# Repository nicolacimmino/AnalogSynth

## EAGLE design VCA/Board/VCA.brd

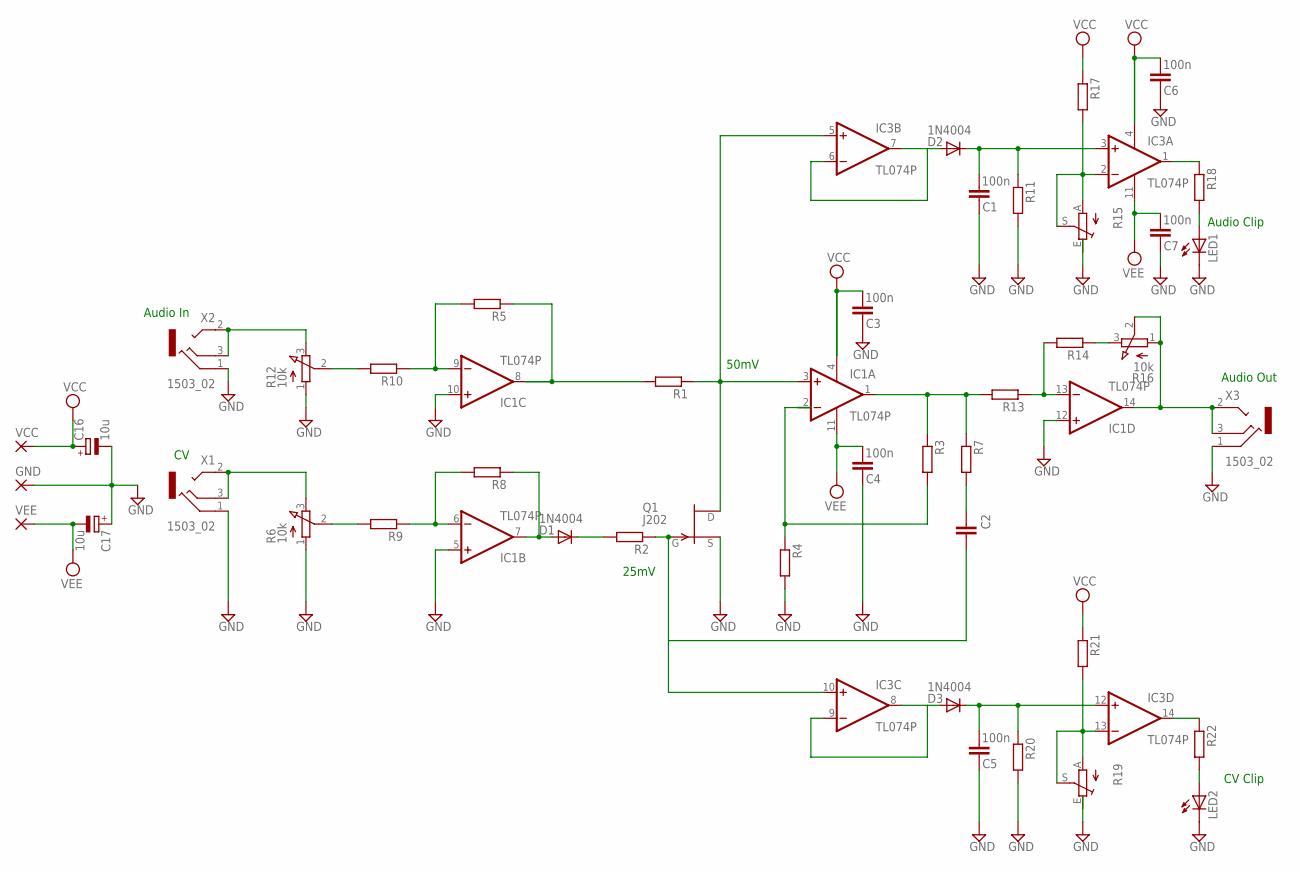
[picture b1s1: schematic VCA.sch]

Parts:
C1, C3, C4, C5, C6, C7: 100n; C5B2.5
C2: C-EU050-045X075; C050-045X075
C16, C17: 10u; E2,5-7
D1, D2, D3: 1N4004; DO41-10
GND: 3,17/1,1
IC1, IC3: TL074P; DIL14
LED1, LED2: LED5MM
Q1: J202; TO92
R1, R2, R3, R4, R5, R7, R8, R9, R10, R11, R13, R14, R17, R18, R20, R21, R22: R-EU_0207/10; 0207/10
R6, R12, R16: 10k; 3RP/1610N
R15, R19: TRIM_EU-S75P; S75P
VCC: 3,17/1,1
VEE: 3,17/1,1
X1, X2, X3: 1503_02

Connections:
GND: C1.1, C3.1, C4.1, C5.1, C6.1, C7.1, C16.-, C17.+, GND.1, IC1.5 (+IN), IC1.10 (+IN), IC1.12 (+IN), LED1.K (C), LED2.K (C), Q1.2 (S), R4.2, R6.1 (A), R11.2, R12.1 (A), R20.2, X1.1, X2.1, X3.1
unnamed: IC1.3 (+IN), IC3.5 (+IN), Q1.3 (D), R1.1
unnamed: C2.2, IC3.10 (+IN), Q1.1 (G), R2.1
unnamed: IC1.2 (-IN), R3.2, R4.1
unnamed: IC1.1 (OUT), R3.1, R7.1, R13.2
unnamed: C2.1, R7.2
unnamed: R6.2 (S), R9.2
unnamed: D1.A, IC1.7 (OUT), R8.1
unnamed: IC1.6 (-IN), R8.2, R9.1
unnamed: D1.C, R2.2
unnamed: R12.3 (E), X2.2, X2.3
unnamed: IC1.8 (OUT), R1.2, R5.1
unnamed: IC1.9 (-IN), R5.2, R10.1
unnamed: R10.2, R12.2 (S)
unnamed: IC1.13 (-IN), R13.1, R14.2
unnamed: R6.3 (E), X1.2, X1.3
unnamed: R14.1, R16.3 (E)
unnamed: IC1.14 (OUT), R16.1 (A), R16.2 (S), X3.2, X3.3
unnamed: D2.A, IC3.6 (-IN), IC3.7 (OUT)
unnamed: C1.2, D2.C, IC3.3 (+IN), R11.1
unnamed: IC3.2 (-IN), R15.A, R15.S, R17.2
unnamed: IC3.1 (OUT), R18.1
unnamed: LED1.A, R18.2
unnamed: D3.A, IC3.8 (OUT), IC3.9 (-IN)
unnamed: C5.2, D3.C, IC3.12 (+IN), R20.1
unnamed: IC3.13 (-IN), R19.A, R19.S, R21.2
unnamed: IC3.14 (OUT), R22.1
unnamed: LED2.A, R22.2
V+: IC3.4 (V+)
V-: IC3.11 (V-)
VCC: C3.2, C6.2, C16.+, IC1.4 (V+), R17.1, R21.1, VCC.1
VEE: C4.2, C7.2, C17.-, IC1.11 (V-), VEE.1

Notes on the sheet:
50mV
25mV
Audio In
Audio Out
Audio Clip
CV Clip

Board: 2 copper layers, 49 parts (0 on the bottom side), 30 nets, no tracks yet.

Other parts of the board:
U$1, U$2, U$3, U$4: 3,2

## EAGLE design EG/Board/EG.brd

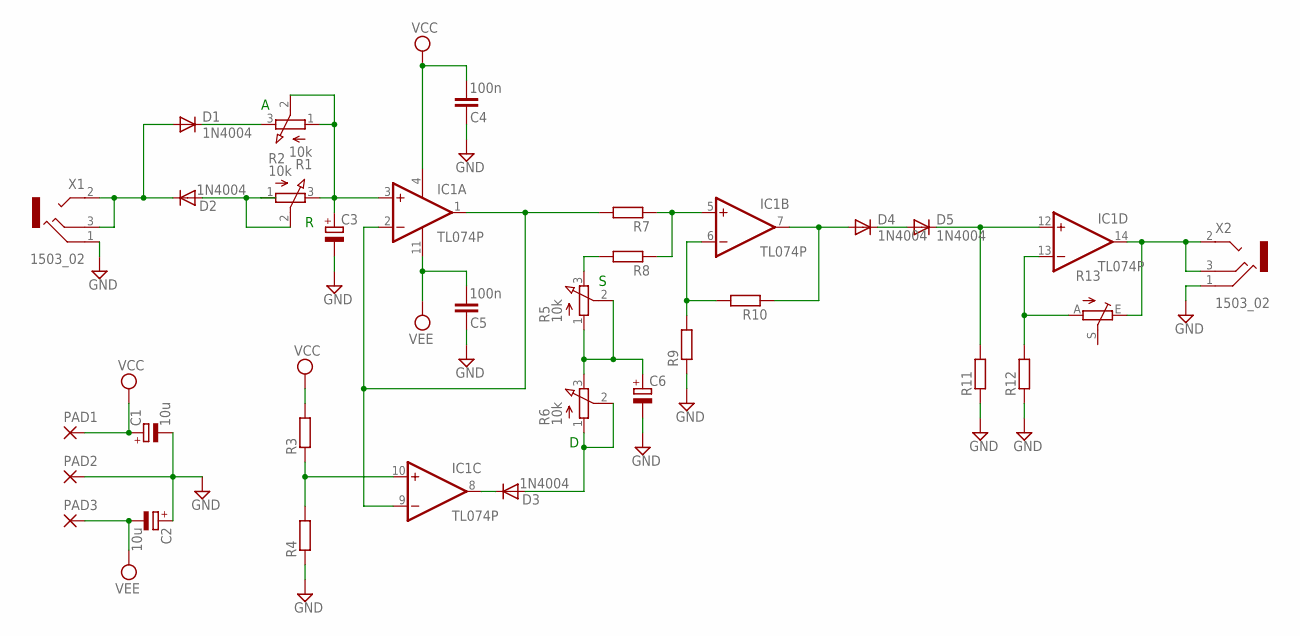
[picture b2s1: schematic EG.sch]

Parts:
C1, C2: 10u; E2,5-7
C3, C6: CPOL-EUE2.5-6; E2,5-6
C4, C5: 100n; C5B2.5
D1, D2, D3, D4, D5: 1N4004; DO41-10
IC1: TL074P; DIL14
PAD1, PAD2, PAD3: 3,17/1,1
R1, R2, R5, R6: 10k; 3RP/1610N
R3, R4, R7, R8, R9, R10, R11, R12: R-EU_0207/10; 0207/10
R13: TRIM_EU-S75P; S75P
X1, X2: 1503_02

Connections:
GND: C1.-, C2.+, C3.-, C4.1, C5.1, C6.-, PAD2.1, R4.1, R9.1, R11.1, R12.1, X1.1, X2.1
unnamed: D1.A, D2.C, X1.2, X1.3
unnamed: D2.A, R2.1 (A), R2.2 (S)
unnamed: IC1.1 (OUT), IC1.2 (-IN), IC1.9 (-IN), R7.2
unnamed: D1.C, R1.3 (E)
unnamed: IC1.6 (-IN), R9.2, R10.2
unnamed: D4.A, IC1.7 (OUT), R10.1
unnamed: IC1.5 (+IN), R7.1, R8.1
unnamed: C3.+, IC1.3 (+IN), R1.1 (A), R1.2 (S), R2.3 (E)
unnamed: R5.3 (E), R8.2
unnamed: C6.+, R5.1 (A), R5.2 (S), R6.3 (E)
unnamed: D3.A, R6.1 (A), R6.2 (S)
unnamed: D3.C, IC1.8 (OUT)
unnamed: IC1.10 (+IN), R3.1, R4.2
unnamed: D4.C, D5.A
unnamed: D5.C, IC1.12 (+IN), R11.2
unnamed: IC1.13 (-IN), R12.2, R13.A
unnamed: IC1.14 (OUT), R13.E, X2.2, X2.3
VCC: C1.+, C4.2, IC1.4 (V+), PAD1.1, R3.2
VEE: C2.-, C5.2, IC1.11 (V-), PAD3.1

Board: 2 copper layers, 34 parts (0 on the bottom side), 20 nets, no tracks yet.

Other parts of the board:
U$1, U$2, U$3, U$4: 3,2

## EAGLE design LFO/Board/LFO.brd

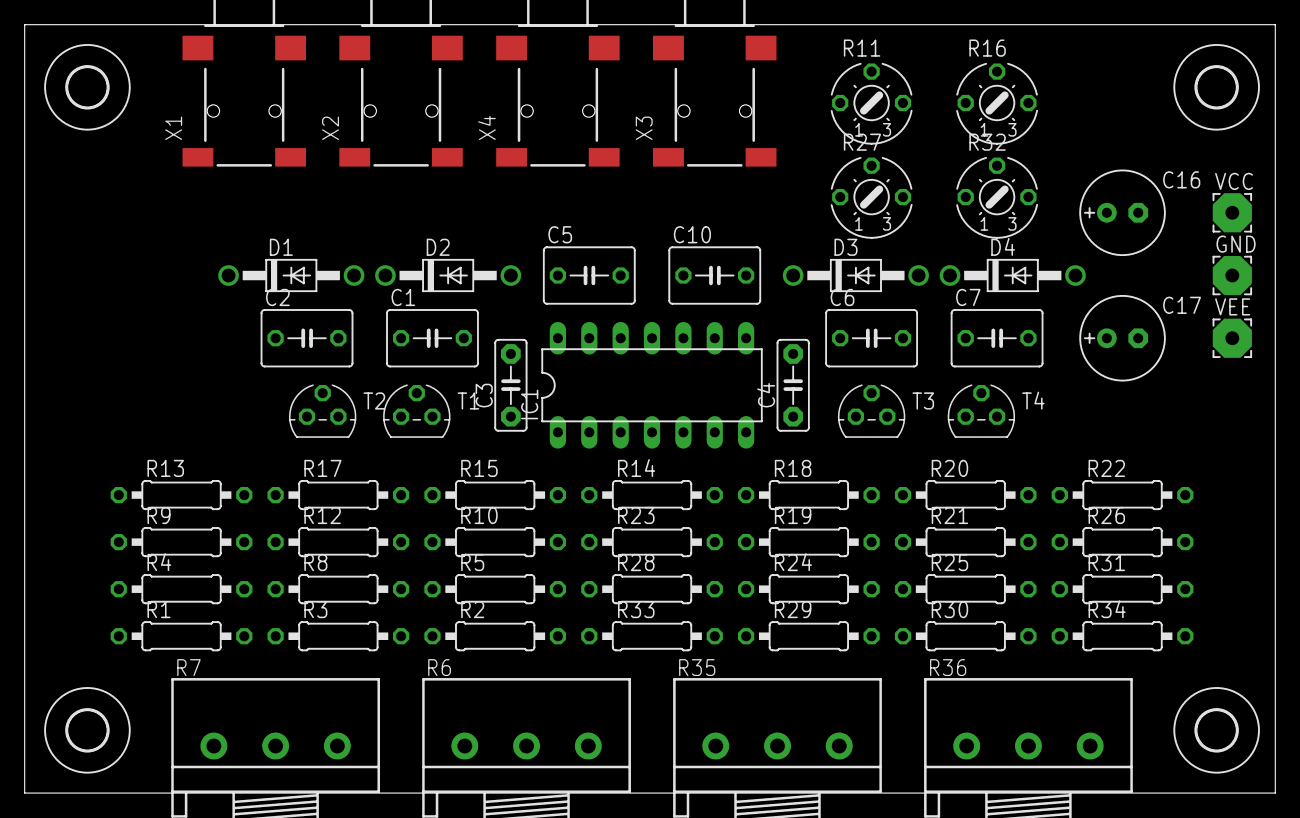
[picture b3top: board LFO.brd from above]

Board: 2 copper layers, 101.3 x 62.2 mm, 66 parts (0 on the bottom side), 41 nets, no tracks yet.

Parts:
C1, C2, C5, C6, C7, C10: C050-045X075
C3, C4: 100n; C5B2.5
C16, C17: 10u; E2,5-7
D1, D2, D3, D4: 1N4004; DO41-10
GND: 3,17/1,1
IC1: TL074P; DIL14
R1, R2, R3, R4, R5, R8, R9, R10, R12, R13, R14, R15, R17, R18, R19, R20, R21, R22, R23, R24, R25, R26, R28, R29, R30, R31, R33, R34: 0207/10
R6, R7, R35, R36: 10k; 3RP/1610N
R11, R16, R27, R32: S75P
T1, T2, T3, T4: BC237; TO92
U$1, U$2, U$3, U$4: 3,2
VCC: 3,17/1,1
VEE: 3,17/1,1
X1, X2, X3, X4: 1503_02

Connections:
GND: C16.-, C17.+, GND.1, IC1.5, IC1.12, R10.1, R13.1, R18.1, R26.1, R29.1, R34.1, T1.1, T2.1, T3.1, T4.1, X1.1, X2.1, X3.1, X4.1
unnamed: C2.2, R2.1, T2.2
unnamed: C2.1, D2.A, R3.1
unnamed: D1.C, R5.1, T2.3
unnamed: C1.2, D1.A, R1.1
unnamed: C1.1, R4.2, T1.2
unnamed: D2.C, IC1.2, R8.1, T1.3
unnamed: R4.1, R7.3
unnamed: R2.2, R7.1
unnamed: R6.2, R6.3, R7.2
unnamed: R16.S, X2.2, X2.3
unnamed: IC1.3, R9.1, R10.2
unnamed: R11.A, R13.2
unnamed: IC1.1, R12.2, R14.1
unnamed: R11.E, R12.1
unnamed: R11.S, X1.2, X1.3
unnamed: C5.1, IC1.7, R15.1, R17.2
unnamed: C5.2, IC1.6, R14.2, R15.2
unnamed: D3.C, R23.1, T4.3
unnamed: C6.2, D3.A, R19.1
unnamed: R16.A, R18.2
unnamed: R16.E, R17.1
unnamed: C6.1, R22.2, T3.2
unnamed: C7.2, R20.1, T4.2
unnamed: C7.1, D4.A, R21.1
unnamed: D4.C, IC1.9, R24.1, T3.3
unnamed: R22.1, R36.3
unnamed: R20.2, R36.1
unnamed: R35.2, R35.3, R36.2
unnamed: IC1.10, R25.1, R26.2
unnamed: IC1.8, R28.2, R30.1
unnamed: R27.A, R29.2
unnamed: R27.E, R28.1
unnamed: C10.1, IC1.14, R31.1, R33.2
unnamed: C10.2, IC1.13, R30.2, R31.2
unnamed: R32.A, R34.2
unnamed: R32.E, R33.1
unnamed: R27.S, X3.2, X3.3
unnamed: R32.S, X4.2, X4.3
VCC: C16.+, IC1.4, R1.2, R3.2, R5.2, R8.2, R9.2, R19.2, R21.2, R23.2, R24.2, R25.2, VCC.1
VEE: C17.-, IC1.11, VEE.1

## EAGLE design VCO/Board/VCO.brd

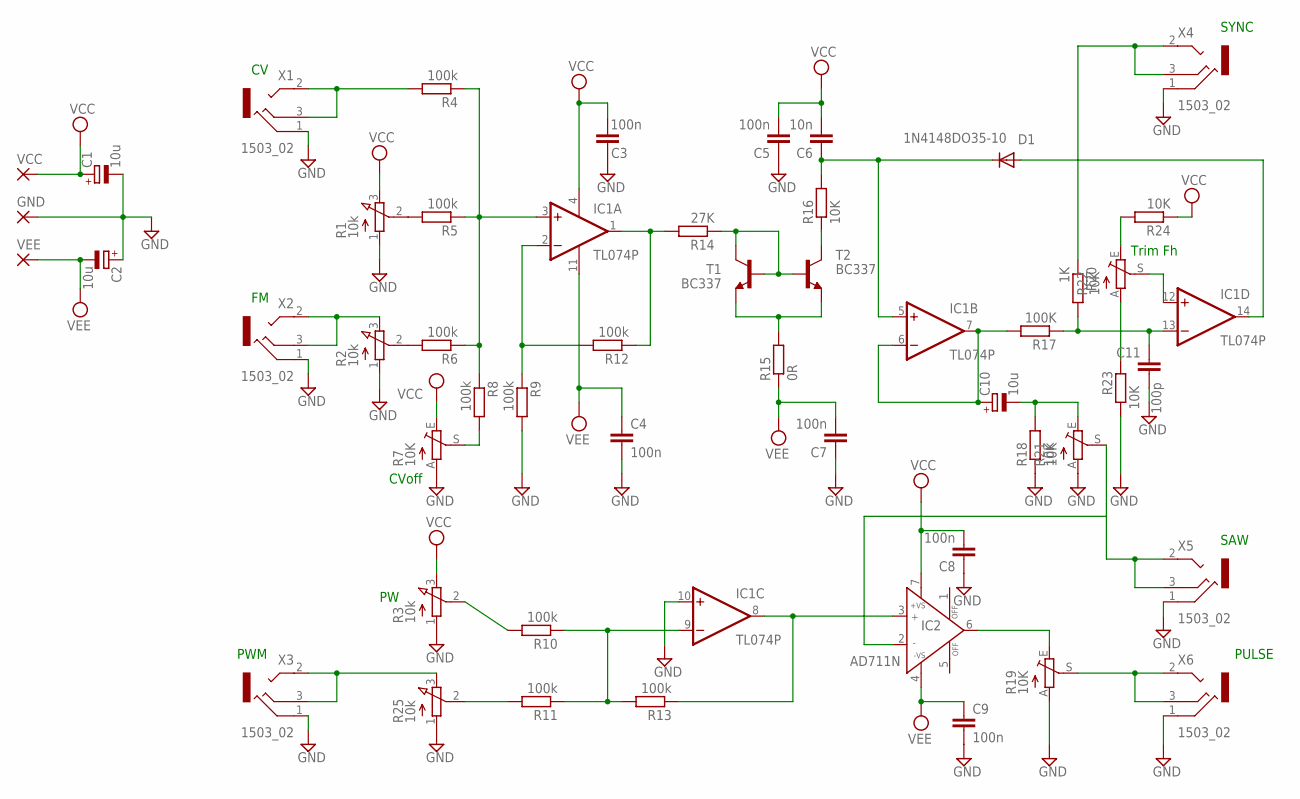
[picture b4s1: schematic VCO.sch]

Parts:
C1, C2, C10: 10u; E2,5-7
C3, C4, C5, C7, C8, C9: 100n; C5B2.5
C6: 10n; C5B2.5
C11: 100p; C2.5-2
D1: 1N4148DO35-10; DO35-10
GND: 3,17/1,1
IC1: TL074P; DIL14
IC2: AD711N; DIL08
R1, R2, R3, R25: 10k; 3RP/1610N
R4, R5, R6, R8, R9, R10, R11, R12, R13: 100k; 0207/10
R7, R19, R21, R22: 10K; CA6V
R14: 27K; 0207/10
R15: 0R; 0207/10
R16, R18, R23, R24: 10K; 0207/10
R17: 100K; 0207/10
R20: 1K; 0207/10
T1, T2: BC337; TO92
VCC: 3,17/1,1
VEE: 3,17/1,1
X1, X2, X3, X4, X5, X6: 1503_02

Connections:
GND: C1.-, C2.+, C3.1, C4.2, C5.1, C7.1, C8.1, C9.2, C11.1, GND.1, IC1.10 (+IN), R1.1 (A), R2.1 (A), R3.1 (A), R7.A, R9.2, R18.1, R19.A, R21.A, R23.1, R25.1 (A), X1.1, X2.1, X3.1, X4.1, X5.1, X6.1
unnamed: R14.1, T1.2 (B), T1.3 (C), T2.2 (B)
unnamed: R15.2, T1.1 (E), T2.1 (E)
unnamed: C6.1, D1.C, IC1.5 (+IN), R16.2
unnamed: R16.1, T2.3 (C)
unnamed: D1.A, IC1.14 (OUT)
unnamed: IC1.12 (+IN), R22.S
unnamed: C11.2, IC1.13 (-IN), R17.1, R20.2
unnamed: C10.+, IC1.6 (-IN), IC1.7 (OUT), R17.2
unnamed: R22.A, R23.2
unnamed: R7.S, R8.2
unnamed: R22.E, R24.2
unnamed: R4.2, X1.2, X1.3
unnamed: IC1.3 (+IN), R4.1, R5.1, R6.1, R8.1
unnamed: R2.2 (S), R6.2
unnamed: R20.1, X4.2, X4.3
unnamed: R11.2, R25.2 (S)
unnamed: R1.2 (S), R5.2
unnamed: IC1.1 (OUT), R12.1, R14.2
unnamed: IC1.2 (-IN), R9.1, R12.2
unnamed: IC2.2 (IN-), R21.S, X5.2, X5.3
unnamed: IC2.6 (OUT), R19.E
unnamed: R19.S, X6.3
unnamed: IC1.9 (-IN), R10.1, R11.1, R13.2
unnamed: C10.-, R18.2, R21.E
unnamed: R2.3 (E), X2.2, X2.3
unnamed: R3.2 (S), R10.2
unnamed: R25.3 (E), X3.2, X3.3
unnamed: IC1.8 (OUT), IC2.3 (IN+), R13.1
V+: IC1.4 (V+)
V-: IC1.11 (V-)
VCC: C1.+, C3.2, C5.2, C6.2, C8.2, IC2.7 (+VS), R1.3 (E), R3.3 (E), R7.E, R24.1, VCC.1
VEE: C2.-, C4.1, C7.2, C9.1, IC2.4 (-VS), R15.1, VEE.1

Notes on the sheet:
Trim Fh
CVoff
SAW
PULSE
PWM
SYNC

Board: 2 copper layers, 54 parts (0 on the bottom side), 31 nets, no tracks yet.

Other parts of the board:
U$1, U$2, U$3, U$4: 3,2

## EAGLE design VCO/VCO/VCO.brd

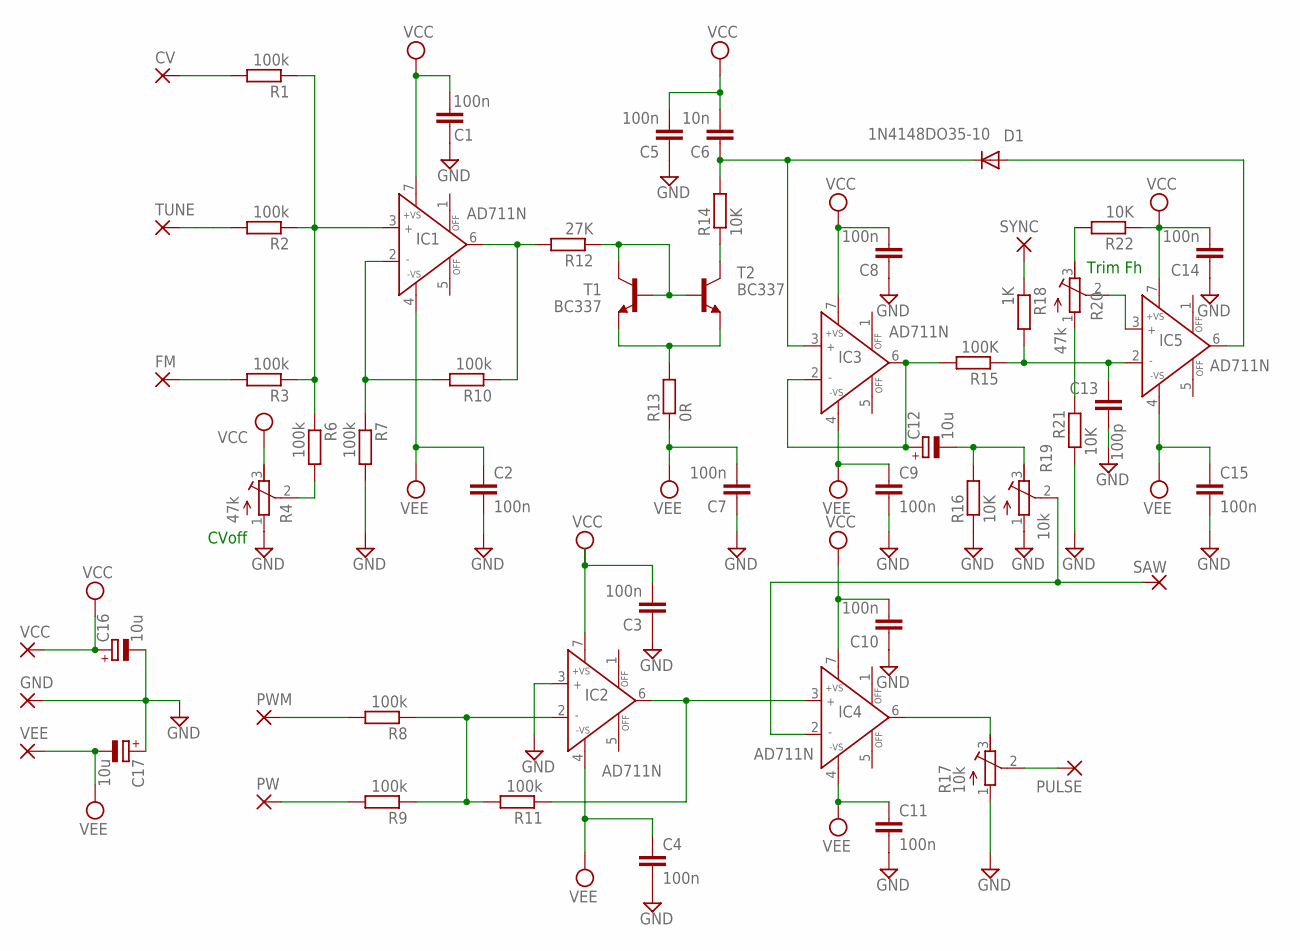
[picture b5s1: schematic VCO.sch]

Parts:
C1, C2, C3, C4, C5, C7, C8, C9, C10, C11, C14, C15: 100n; C5B2.5
C6: 10n; C5B2.5
C12, C16, C17: 10u; E2,5-7
C13: 100p; C2.5-2
CV: 3,17/1,1
D1: 1N4148DO35-10; DO35-10
FM: 3,17/1,1
GND: 3,17/1,1
IC1, IC2, IC3, IC4, IC5: AD711N; DIL08
PULSE: 3,17/1,1
PW: 3,17/1,1
PWM: 3,17/1,1
R1, R2, R3, R6, R7, R8, R9, R10, R11: 100k; 0207/10
R4, R20: 47k; RTRIM64W
R12: 27K; 0207/10
R13: 0R; 0207/10
R14, R16, R21, R22: 10K; 0207/10
R15: 100K; 0207/10
R17, R19: 10k; RTRIM3339P
R18: 1K; 0207/10
SAW: 3,17/1,1
SYNC: 3,17/1,1
T1, T2: BC337; TO92
TUNE: 3,17/1,1
VCC: 3,17/1,1
VEE: 3,17/1,1

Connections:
GND: C1.1, C2.2, C3.1, C4.2, C5.1, C7.1, C8.1, C9.2, C10.1, C11.2, C13.1, C14.1, C15.2, C16.-, C17.+, GND.1, IC2.3 (IN+), R4.1 (A), R7.2, R16.1, R17.1 (A), R19.1 (A), R21.1
unnamed: R12.1, T1.2 (B), T1.3 (C), T2.2 (B)
unnamed: R13.2, T1.1 (E), T2.1 (E)
unnamed: C6.1, D1.C, IC3.3 (IN+), R14.2
unnamed: R14.1, T2.3 (C)
unnamed: D1.A, IC5.6 (OUT)
unnamed: IC5.3 (IN+), R20.2 (S)
unnamed: C13.2, IC5.2 (IN-), R15.1, R18.2
unnamed: C12.+, IC3.2 (IN-), IC3.6 (OUT), R15.2
unnamed: R20.1 (A), R21.2
unnamed: R4.2 (S), R6.2
unnamed: R20.3 (E), R22.2
unnamed: CV.1, R1.2
unnamed: IC1.3 (IN+), R1.1, R2.1, R3.1, R6.1
unnamed: FM.1, R3.2
unnamed: R18.1, SYNC.1
unnamed: R2.2, TUNE.1
unnamed: IC1.6 (OUT), R10.1, R12.2
unnamed: IC1.2 (IN-), R7.1, R10.2
unnamed: IC4.2 (IN-), R19.2 (S), SAW.1
unnamed: IC4.6 (OUT), R17.3 (E)
unnamed: PULSE.1, R17.2 (S)
unnamed: IC2.2 (IN-), R8.1, R9.1, R11.2
unnamed: C12.-, R16.2, R19.3 (E)
unnamed: PWM.1, R8.2
unnamed: PW.1, R9.2
unnamed: IC2.6 (OUT), IC4.3 (IN+), R11.1
VCC: C1.2, C3.2, C5.2, C6.2, C8.2, C10.2, C14.2, C16.+, IC1.7 (+VS), IC2.7 (+VS), IC3.7 (+VS), IC4.7 (+VS), IC5.7 (+VS), R4.3 (E), R22.1, VCC.1
VEE: C2.1, C4.1, C7.2, C9.1, C11.1, C15.1, C17.-, IC1.4 (-VS), IC2.4 (-VS), IC3.4 (-VS), IC4.4 (-VS), IC5.4 (-VS), R13.1, VEE.1

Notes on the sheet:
Trim Fh
CVoff

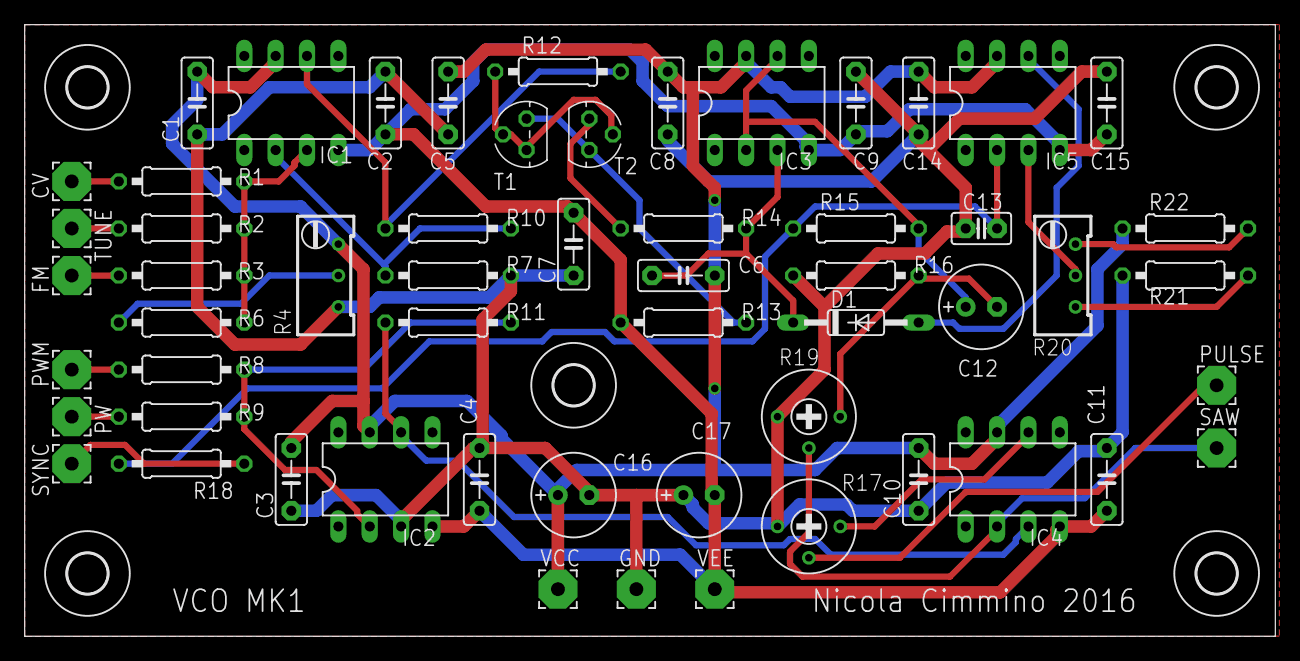
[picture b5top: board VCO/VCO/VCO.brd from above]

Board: 2 copper layers, 101.3 x 49.5 mm, 62 parts (0 on the bottom side), 29 nets.

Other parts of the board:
U$1, U$2, U$3, U$4, U$5: 3,2

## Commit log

2016-03-28 Add schematic and sym
2016-04-03 First VCO schematic simulation
2016-04-03 Rename READ.me to README.md
2016-04-17 Add schematic, fft, update simulation
2016-04-17 Update simulation, add conrol lin graph
2016-04-17 Update simulation graphs
2016-04-19 Simulation update, vctrl vs freq study
2016-04-23 Update schematic
2016-04-25 Schematic update
2016-05-09 Schema update
2016-05-13 Board first layout
2016-05-21 Clean up
2016-05-21 Update gitignore
2016-05-21 Shuffle folders
2016-05-21 Add LFO
2016-05-22 Change VCO connectors
2016-05-22 Progress LFO schematic
2016-05-22 Change VCO to use TL074
2016-05-24 Tweks to reduce BOM cost
2016-05-24 Add PWM pot
2016-05-24 Update schematic and board images
2016-05-27 Progress LFO board
2016-05-29 Envelope Generator
2016-05-29 Cleanup
2016-05-29 Fix folder
2016-05-30 Avoid bounce back after release
2016-05-30 EG Schematic and board
2016-06-19 Add vca, cleanup
2016-06-30 Add VCA schematic
2016-07-14 Add clip indicator to VCA
2016-07-14 VCA board
